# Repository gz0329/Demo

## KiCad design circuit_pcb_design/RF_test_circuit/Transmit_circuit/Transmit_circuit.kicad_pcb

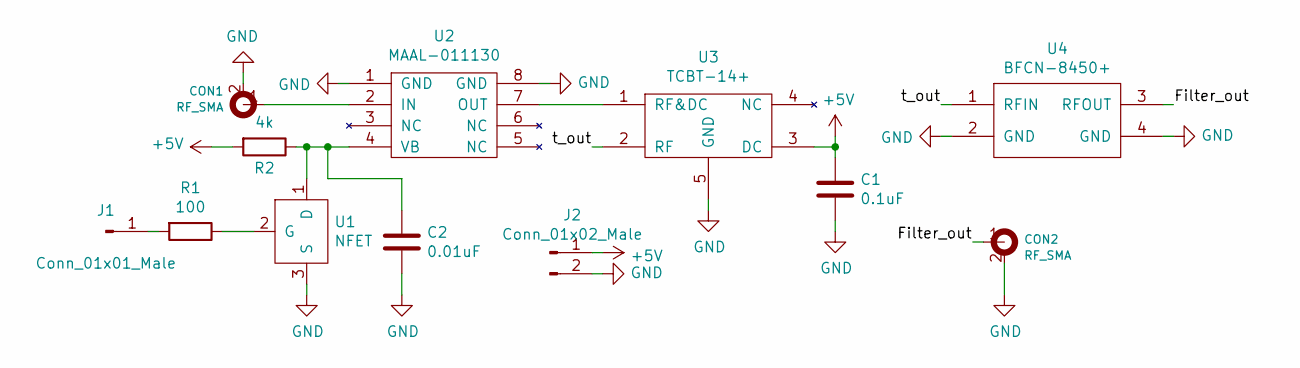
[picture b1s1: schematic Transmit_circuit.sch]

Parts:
C1: 0.1uF; C_0402
C2: 0.01uF; C_0603
CON1, CON2: RF_SMA; SMAConnector
J1: Conn_01x01_Male; PinHeader_1x01_P2.54mm_Vertical
J2: Conn_01x02_Male; PinHeader_1x02_P2.54mm_Vertical
R1: 100; R_0402
R2: 4k; R_0201_0603Metric
U1: NFET
U2: MAAL-011130
U3: TCBT-14+
U4: BFCN-8450+

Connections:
+5V: C1.1, J2.1, R2.2, U3.3 (DC)
/Filter_out: CON2.1, U4.3 (RFOUT)
/t_out: U3.2 (RF), U4.1 (RFIN)
GND: C1.2, C2.2, CON1.2, CON2.2, J2.2, U1.3 (S), U2.1 (GND), U2.8 (GND), U3.5 (GND), U4.2 (GND), U4.4 (GND)
unnamed: C2.1, R2.1, U1.1 (D), U2.4 (VB)
unnamed: CON1.1, U2.2 (IN)
unnamed: J1.1, R1.2
unnamed: R1.1, U1.2 (G)
unnamed: U2.7 (OUT), U3.1 (RF&DC)

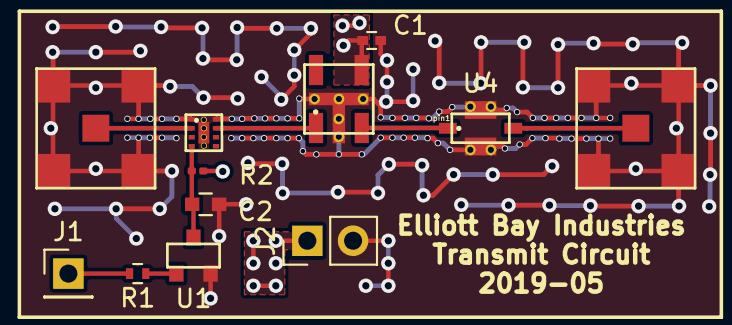
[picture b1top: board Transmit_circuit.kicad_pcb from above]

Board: 4 copper layers, 12 parts (0 on the bottom side), 9 nets.
